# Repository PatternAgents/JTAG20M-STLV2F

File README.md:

JTAG20M-STLV2F
==============

ST-Link./V2 to JTAG 20 Pin Male Adapter

[  
*PatternAgents JTAG20M-STLV2F*](http://www.patternagents.com/projects/JTAG20M-STLV2F.html)

The PatternAgents JTAG20M-STLV2F.

Features:

[  
*Licensing CC BY-NC-SA 4.0*](http://creativecommons.org/licenses/by-nc-sa/4.0/)

PatternAgents uses the increasingly popular business model called "Dual Licensing" 
in which both the open source software distribution mechanism and traditional commercial software distribution models are combined.

Open Source Projects:        

If you are developing and distributing open source applications under the Creative Commons CC BY-NC-SA 4.0, 
as published by the Creative Commons Foundation, then you are free to use the PatternAgents hardware/software under the CC BY-NC-SA 4.0 license. 
Please note that CC BY-NC-SA 4.0 requires that all modifications to the original code as well as all Derivative Works 
must also be released under the terms of the CC BY-NC-SA 4.0 license.

Closed Source Projects:

If you are developing and distributing traditional closed source or commercial applications, 
you must purchase a PatternAgents commercial use license, 
which is specifically designed for users interested in retaining the proprietary status of their designs and code. 
All PatternAgents commercial licenses expressly supersede the CC BY-NC-SA 4.0 license. 
This means that when you license the PatternAgents software under a commercial license, 
you specifically do not use the software under the CC BY-NC-SA 4.0 license and therefore you are not subject to any of its terms.
        
If you would like to use our designs for your own personal or educational use, have at it! 

Our public design repository is available at <a href="https://github.com/patternagents">Github</a>.

If you would like to produce our designs for commercial use, or as products for sale, 
please contact us to arrange for a Commercial Use license. We have many other designs, 
as well as options and extras that are not released publicly. 
We will also customize designs, firmware, and software for a reasonable fee, just contact us to discuss your requirements.

THIS SOFTWARE IS PROVIDED BY THE CONTRIBUTORS "AS IS" AND WITHOUT ANY EXPRESS OR IMPLIED WARRANTIES, 
INCLUDING, BUT NOT LIMITED TO, THE IMPLIED WARRANTIES OF MERCHANTABILITY AND FITNESS FOR A PARTICULAR PURPOSE ARE DISCLAIMED. 
IN NO EVENT SHALL THE COPYRIGHT OWNER OR CONTRIBUTORS BE LIABLE FOR ANY DIRECT, INDIRECT, INCIDENTAL, SPECIAL, EXEMPLARY, 
OR CONSEQUENTIAL DAMAGES (INCLUDING, BUT NOT LIMITED TO, PROCUREMENT OF SUBSTITUTE GOODS OR SERVICES; LOSS OF USE, DATA, 
OR PROFITS; OR BUSINESS INTERRUPTION) HOWEVER CAUSED AND ON ANY THEORY OF LIABILITY, WHETHER IN CONTRACT, 
STRICT LIABILITY, OR TORT (INCLUDING NEGLIGENCE OR OTHERWISE) ARISING IN ANY WAY OUT OF THE USE OF THIS SOFTWARE, 
EVEN IF ADVISED OF THE POSSIBILITY OF SUCH DAMAGE. 

-------------------------------------------------------------------------------------------

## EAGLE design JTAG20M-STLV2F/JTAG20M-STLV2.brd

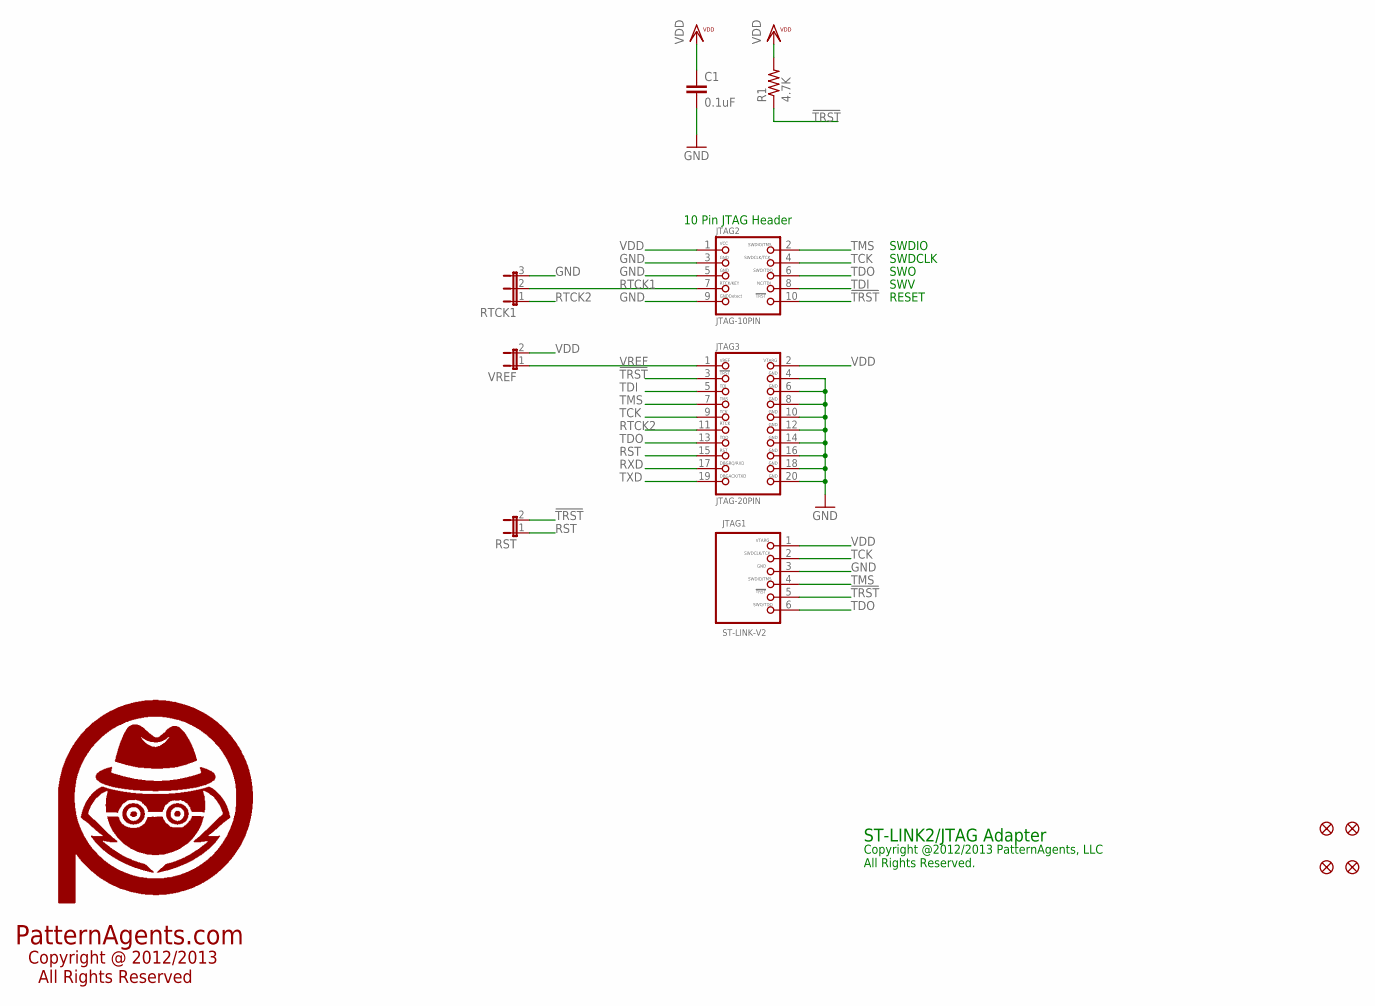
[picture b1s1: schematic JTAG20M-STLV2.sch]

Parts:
C1: 0.1uF; 0603-CAP
FID1, FID2, FID3, FID4: FIDUCIAL1.5X3; FIDUCIAL-1.5X3
JTAG1: ST-LINK-V2; 1X06_2.54MM_PTH
JTAG2: JTAG-10PIN; 2X05_1.27MM_SMT
JTAG3: JTAG-20PIN; 2X10_2.54MM_PTH
R1: 4.7K; 0603-RES
RST: JUMPER2
RTCK1: JUMPER3
U$2: PA_LOGO_SYMLARGE; PA_LOGO_AGENT_LRG_SYM
VREF: JUMPER2

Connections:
!TRST: JTAG1.5, JTAG2.10, JTAG3.3, R1.1, RST.2
GND: C1.2, JTAG1.3, JTAG2.3, JTAG2.5, JTAG2.9, JTAG3.4, JTAG3.6, JTAG3.8, JTAG3.10, JTAG3.12, JTAG3.14, JTAG3.16, JTAG3.18, JTAG3.20, RTCK1.3
RST: JTAG3.15, RST.1
RTCK1: JTAG2.7, RTCK1.2
RTCK2: JTAG3.11, RTCK1.1
RXD: JTAG3.17
TCK: JTAG1.2, JTAG2.4, JTAG3.9
TDI: JTAG2.8, JTAG3.5
TDO: JTAG1.6, JTAG2.6, JTAG3.13
TMS: JTAG1.4, JTAG2.2, JTAG3.7
TXD: JTAG3.19
VDD: C1.1, JTAG1.1, JTAG2.1, JTAG3.2, R1.2, VREF.2
VREF: JTAG3.1, VREF.1

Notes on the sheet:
PatternAgents.com
Copyright @ 2012/2013 All Rights Reserved
ST-LINK2/JTAG Adapter
Copyright @2012/2013 PatternAgents, LLC All Rights Reserved.
SWDIO
SWDCLK
RESET
10 Pin JTAG Header
SWO
SWV

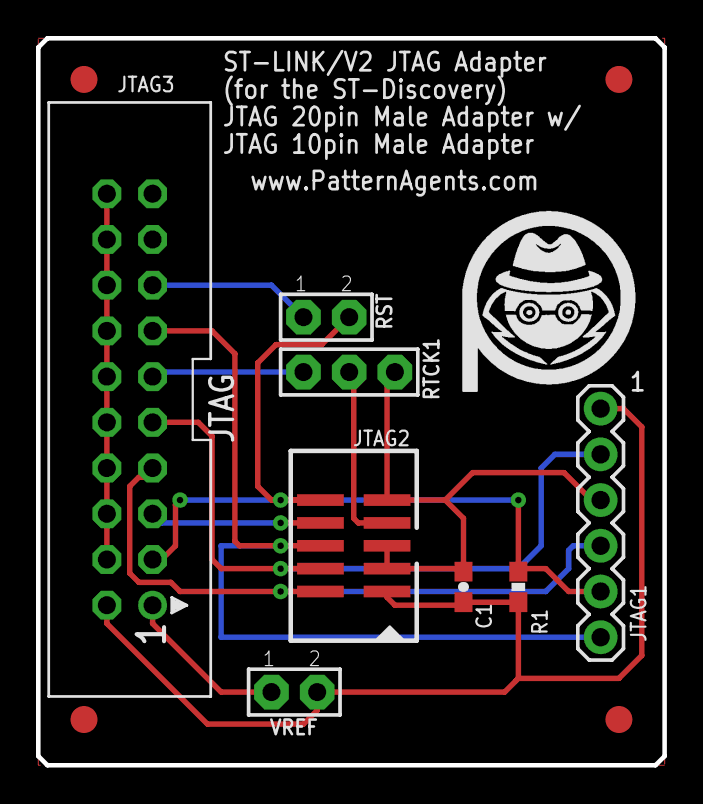
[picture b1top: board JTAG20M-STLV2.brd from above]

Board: 2 copper layers, 34.8 x 40.4 mm, 14 parts (1 on the bottom side), 11 nets.

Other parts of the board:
U$1: PA_LOGO_SYMLARGE; PA_LOGO_AGENT_LRG_SYM

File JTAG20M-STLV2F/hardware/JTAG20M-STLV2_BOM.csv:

"Part";"Value";"Device";"Package";"Description";"";
"C1";"0.1uF";"CAP0603-CAP";"0603-CAP";"Capacitor";"";
"FID1";"FIDUCIAL1.5X3";"FIDUCIAL1.5X3";"FIDUCIAL-1.5X3";"Fiducial Alignment Points";"";
"FID2";"FIDUCIAL1.5X3";"FIDUCIAL1.5X3";"FIDUCIAL-1.5X3";"Fiducial Alignment Points";"";
"FID3";"FIDUCIAL1.5X3";"FIDUCIAL1.5X3";"FIDUCIAL-1.5X3";"Fiducial Alignment Points";"";
"FID4";"FIDUCIAL1.5X3";"FIDUCIAL1.5X3";"FIDUCIAL-1.5X3";"Fiducial Alignment Points";"";
"JTAG1";"ST-LINK-V2";"ST-LINK-V2";"1X06_2.54MM_PTH";"ST-Link/V2 JTAG/SWD Connector";"";
"JTAG2";"JTAG-10PIN";"JTAG-10PINSMD";"2X05_1.27MM_SMT";"JTAG 10 Pin (SWD) Programming Connector";"";
"JTAG3";"JTAG-20PIN";"JTAG-20PIN";"2X10_2.54MM_PTH";"JTAG 20 Pin Programming Connector";"";
"R1";"4.7K";"RESISTOR_SFE0603-RES";"0603-RES";"Resistor";"";
"RST";"";"JUMPER2";"JUMPER2";"Jumper 2 Pin";"";
"RTCK1";"";"JUMPER3";"JUMPER3";"Jumper 3 Pin";"";
"U$2";"PA_LOGO_SYMLARGE";"PA_LOGO_SYMLARGE";"PA_LOGO_AGENT_LRG_SYM";"PatternAgents Logo Symbol";"";
"VREF";"";"JUMPER2";"JUMPER2";"Jumper 2 Pin";"";

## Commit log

2014-04-17 add eagle files

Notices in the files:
parts and their libraries:
PatternAgents-Logos: License : http://creativecommons.org/licenses/by-sa/3.0
(Creative Commons 3.0)
